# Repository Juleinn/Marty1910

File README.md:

# Marty 1910 bluetooth interface firmware

This repository stores the firmware for getting old marty 1910 phones back to life with a ag1171 and bm64 modules (SLIC and Bluetooth modules).

- Vidéo :   

- Hackaday.io : [Marty 1910 adapter](https://hackaday.io/project/181056-marty-1910-magneto-phone-bluetooth-adapter)

## Contents
<!-- vim-markdown-toc GitLab -->

* [requirements](#requirements)
* [Configuring the BM64 module](#configuring-the-bm64-module)
* [directory structure](#directory-structure)
* [Firmware description](#firmware-description)

<!-- vim-markdown-toc -->

## requirements
- esp-idf : https://docs.espressif.com/projects/esp-idf/en/latest/esp32/get-started/index.html#installation-step-by-step
- ftdi (for flashing and install)

## Configuring the BM64 module
The BM64 modules requires configuration prior to using it. The configuration process is detailed here : https://github.com/danjulio/blue_pot#bm64-configuration, and this project works with the exact same BM64 configuration as the Blue POT project.

## directory structure
```bash
tree main
main
├── ag1171_driver.c // SLIC driver, including RING signal generation & hangup detection
├── ag1171_driver.h
├── bm64_driver.c // BM64 driver : incomming call events, place calls, ...
├── bm64_driver.h
├── bm64_strings.h
├── CMakeLists.txt
├── component.mk
├── firmware_main.c // main logic
├── line.c  // cranking detection and line relay driving
└── line.h
```

```bash
tree hardware
hardware
├── bluetooth.brd # PCB design
├── bluetooth.csv # list of components
└── bluetooth.sch # schematic
```

## Firmware description

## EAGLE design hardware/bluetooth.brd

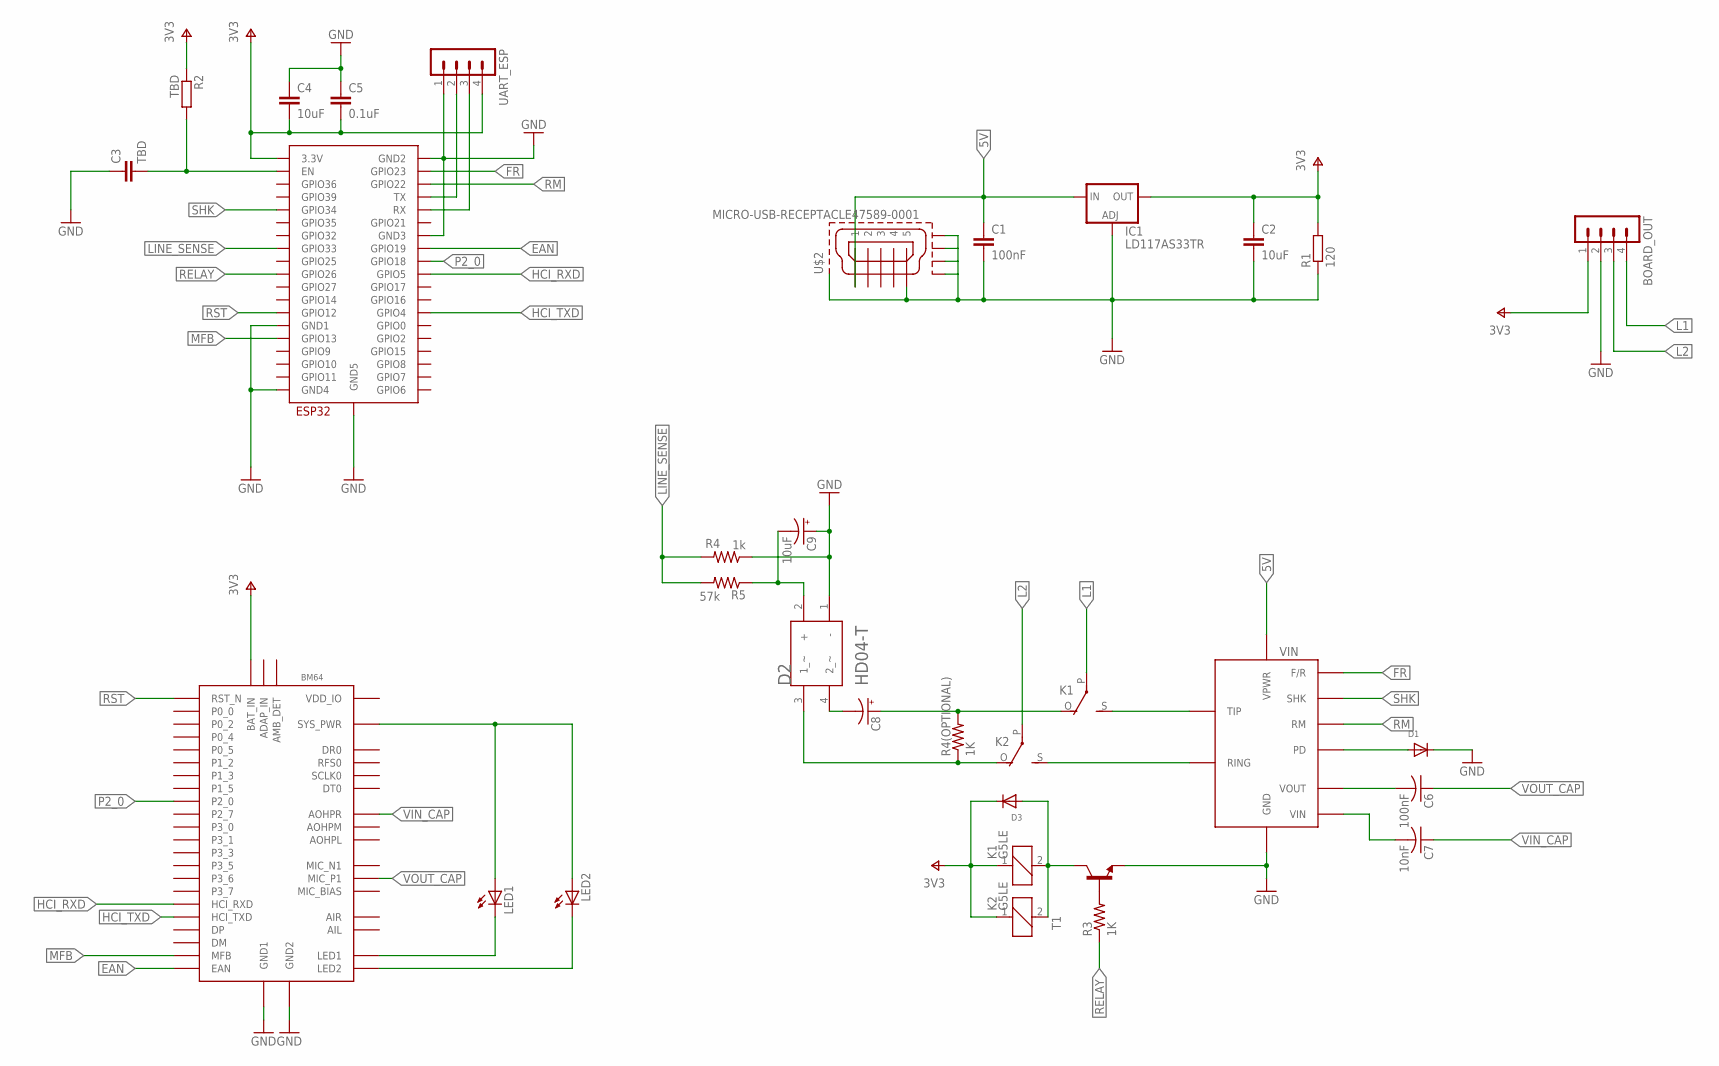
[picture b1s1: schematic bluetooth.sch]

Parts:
BM64: DJD_EAGLE_LIBRARY_BM64
BOARD_OUT: MA04-1
C1, C6: 100nF; C0805
C2, C4: 10uF; C0805
C3: TBD; C0805
C5: 0.1uF; C0805
C7: 10nF; C0805
C8: CPOL-USE2-5; E2-5
C9: 10uF; CPOL-RADIAL-2.5MM-5MM
D1: DIODESMA; SMADIODE
D2: DIODES_HD04-TDIODES_HD04-T_0_0; DIODES_HD04-T_0
D3: DIODESOD-123; SOD-123
IC1: LD117AS33TR; SOT223
K1, K2: G5LE
LED1, LED2: LEDCHIP-LED0805; CHIP-LED0805
R1: 120; M0805
R2: TBD; M0805
R3, R4(OPTIONAL): 1K; M0805
R4: 1k; M0805
R5: 57k; M0805
T1: -NPN-SOT23-EBC; SOT23-EBC
U$1: ESP32-WROOM
U$2: MICRO-USB-RECEPTACLE47589-0001; 47589-0001
UART_ESP: MA04-1
VIN: DJD_EAGLE_LIBRARY_AG1171SIL; DJD_EAGLE_LIBRARY_AG1171

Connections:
5V: C1.1, IC1.3 (IN), U$2.1, VIN.P$13 (VPWR)
ADAP_IN: BM64.23 (ADAP_IN)
CRANK_LOAD_1: C8.+, K1.O, R4(OPTIONAL).2
CRANK_LOAD_2: D2.3 (1_~), K2.O, R4(OPTIONAL).1
EAN: BM64.32 (EAN), U$1.IO19 (GPIO19)
ESP_EN: C3.2, R2.2, U$1.EN
ESP_RX: U$1.RX, UART_ESP.3
ESP_TX: U$1.TX, UART_ESP.2
FR: U$1.IO23 (GPIO23), VIN.P$3 (F/R)
GND: BM64.14 (GND1), BM64.43 (GND2), BOARD_OUT.2, C1.2, C2.2, C3.1, C4.1, C5.1, C9.1 (+), D1.C, D2.1 (-), IC1.1 (ADJ), R1.1, R4.1, T1.E, U$1.GND1, U$1.GND2, U$1.GND3, U$1.GND4, U$1.GND5, U$2.5, U$2.CASING1 (GND1), U$2.CASING2 (GND2), U$2.CASING3 (GND3), U$2.CASING4 (GND4), UART_ESP.1, VIN.P$12 (GND)
HCI_RXD: BM64.19 (HCI_RXD), U$1.IO5 (GPIO5)
HCI_TXD: BM64.20 (HCI_TXD), U$1.IO4 (GPIO4)
L1: BOARD_OUT.4, K1.P
L2: BOARD_OUT.3, K2.P
LED1: BM64.28 (LED1), LED1.C
LED2: BM64.27 (LED2), LED2.C
LINE_RELAY_1: K1.S, VIN.P$2 (TIP)
LINE_RELAY_2: K2.S, VIN.P$1 (RING)
LINE_SENSE: R4.2, R5.2, U$1.IO33 (GPIO33)
MFB: BM64.26 (MFB), U$1.IO13 (GPIO13)
unnamed: R3.2, T1.B
unnamed: C8.-, D2.4 (2_~)
unnamed: C9.2 (-), D2.2 (+), R5.1
P2_0: BM64.41 (P2_0), U$1.IO18 (GPIO18)
POWER_DOWN: D1.A, VIN.P$14 (PD)
RELAY: R3.1, U$1.IO26 (GPIO26)
RELAY_DRIVE: D3.A, K1.2, K2.2, T1.C
RM: U$1.IO22 (GPIO22), VIN.P$4 (RM)
RST: BM64.13 (RST_N), U$1.IO12 (GPIO12)
SHK: U$1.IO34 (GPIO34), VIN.P$5 (SHK)
SYS_PWR: BM64.24 (SYS_PWR), LED1.A, LED2.A
V+: BM64.22 (BAT_IN), BOARD_OUT.1, C2.1, C4.2, C5.2, D3.C, IC1.4 (OUT), K1.1, K2.1, R1.2, R2.1, U$1.3V3 (3.3V), UART_ESP.4
VIN: C7.2, VIN.P$9 (VIN)
VIN_CAP: BM64.5 (AOHPR), C7.1
VOUT: C6.2, VIN.P$10 (VOUT)
VOUT_CAP: BM64.9 (MIC_P1), C6.1

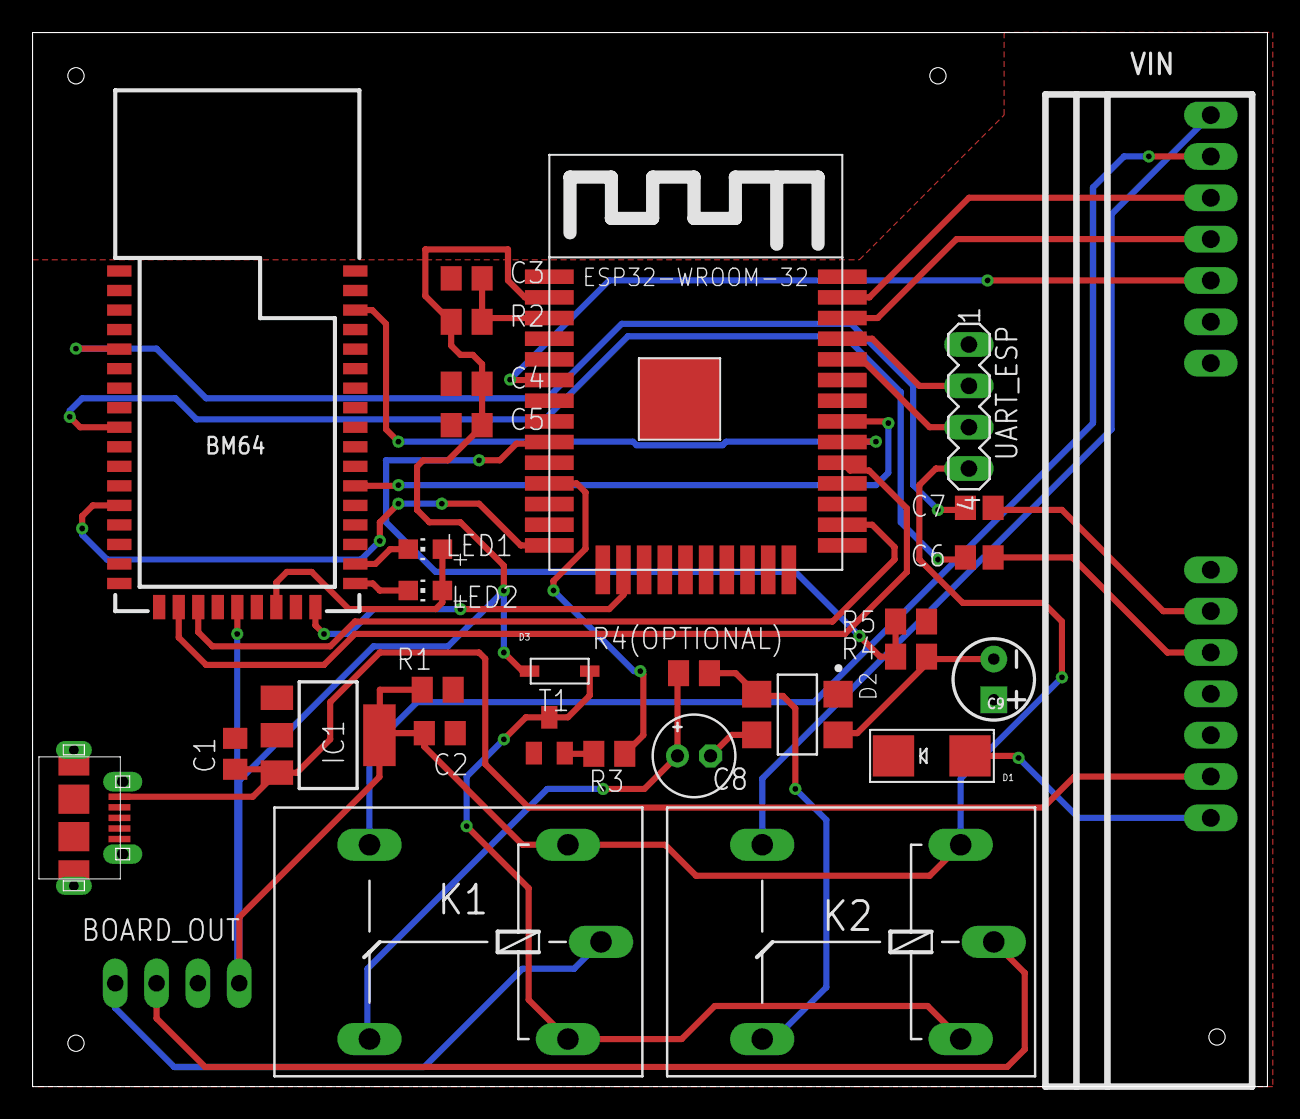
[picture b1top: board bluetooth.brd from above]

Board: 2 copper layers, 75.9 x 64.8 mm, 30 parts (1 on the bottom side), 35 nets.

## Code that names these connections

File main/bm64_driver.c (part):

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#include "freertos/FreeRTOS.h"
#include "freertos/task.h"

#define P2_0        18
#define EAN         19
#define MFB         13
#define RST         12
#define GPIO_OUTPUT_PIN_SEL  ((1ULL<<P2_0) | (1ULL<<EAN) | (1ULL<<MFB) | (1ULL<<RST))

// uart config
#define UART_PORT_NUMBER 2
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
static void bm64_reset(void)
{
    gpio_set_level(MFB, 0);
    gpio_set_level(RST, 0);
    vTaskDelay(499 / portTICK_RATE_MS);

    gpio_set_level(MFB, 1);

    vTaskDelay(1 / portTICK_RATE_MS);

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    io_conf.intr_type = GPIO_INTR_DISABLE;
    //set as output mode
    io_conf.mode = GPIO_MODE_OUTPUT;
    //bit mask of the pins that you want to set,e.g.GPIO18/19
    io_conf.pin_bit_mask = GPIO_OUTPUT_PIN_SEL;
    //disable pull-down mode
    io_conf.pull_down_en = 0;
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    //configure GPIO with the given settings
    gpio_config(&io_conf);

    gpio_set_level(P2_0, 1);
    gpio_set_level(EAN, 0);
    gpio_set_level(MFB, 1);
    gpio_set_level(RST, 1);
}

void bm64_prepare_flash_mode()
{
    bm64_gpio_init();
    gpio_set_level(P2_0, 0);
    gpio_set_level(EAN, 0);
    bm64_reset();
}

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
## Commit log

2020-10-04 Split bm64 driver into separate file
2020-10-04 Add event processing & device name change
2020-10-04 split debug strings into dedicated file
2020-10-04 Add support for call status
2020-10-10 Add test dial
2020-10-17 Add relay
    - add relay on-off sequence
    - add bm64 commands decoding
2020-10-18 Add support for accepting incomming calls
2020-11-05 Add ag1171 driver
2020-11-05 SHK debounce
2020-11-09 Add line (relays) controller
2020-11-09 Add off-hook detection wrapper
2020-11-11 Start implementing main phone logic
2020-11-11 Add ring start/stop as a state. Add SHK trigger
    - Add start_ringing() and stop_ringing() functions to start and stop a state of ringinge
    - Add off-hook detection callback function to be overridden
2020-11-11 Implement ringing & accept call logic
2020-11-11 Add bm64 incomming call callback
    - add weak callback to be overridden to handle incomming call
    - Fix stack overflow on printing bm64 events
    - Fix latency on parsing uart bm64 events
2020-11-11 Add ag1171 on-hook handler
2020-11-11 Add reject and end call wrappers
2020-11-11 Change semaphore to queues
    - handle multiple types of async events from routines with queues instead of semaphores
2020-11-11 Fix stack overflow crash (increase stack size)
2020-11-11 Change event handling
    uint32_t event code to dedicated enum
2020-11-11 Add hang-up on phone on-hook during communication
2020-11-11 Implement going back to idle
    handle idle call status from phone (hang up on smart phone or on caller side) during call aswell as during ringing
2020-11-11 Add support for call cancel during ringing.
    also patch bug on offhook event messaging (need to solve)
2020-11-11 Change end call uart command
    End call/transfer audio -> force end call
2020-11-11 Reduce latency of bm64 events
    Acknowledge bm64 commands after processing to prevent it from waiting 800ms timeout before sending the next event. This increases responsivity a lot.
2020-11-12 Enhance logging
2020-11-12 Fix invalid off-hook detection
    - fix invalid debouncing
    - empty event queues before waiting for new events (removes duplicate events)
2020-11-13 Set gain level on bm64
2020-11-24 Implement outgoing calls originated from the phone
2020-12-05 Change pinout to match PCB
    - Swap UART pins to bm64
    - Swap FR/RM to ag1171
    - Swap relay levels
2020-12-05 Add routine to put bm64 in flash mode
2020-12-06 WIP: Add line crank detection behavior
2021-08-09 Add board, schematic and components
2021-08-09 Add license

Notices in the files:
parts and their libraries:
SparkFun-Capacitors: Licensing: Creative Commons ShareAlike 4.0 International - https://creativecommons.org/licenses/by-sa/4.0
con-molex-usb: (C) 2014 Tomasz Boleslaw CEDRO, cederom@tlen.pl, http://www.tomek.cedro.info.
